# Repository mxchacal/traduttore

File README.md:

# traduttore

https://mxchacal.github.io/traduttore/

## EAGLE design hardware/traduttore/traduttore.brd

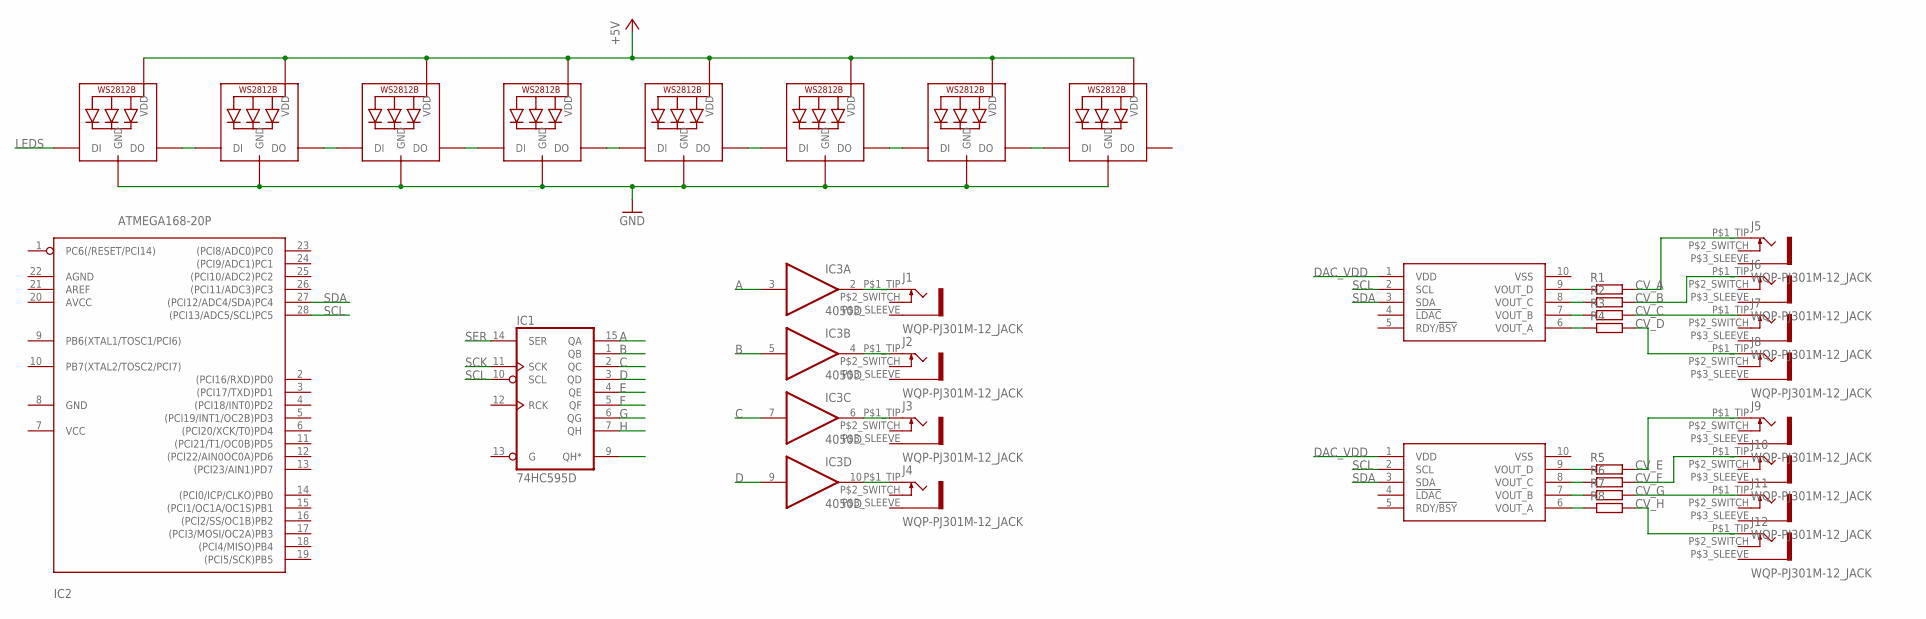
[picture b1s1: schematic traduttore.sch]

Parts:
IC1: 74HC595D; SO16
IC2: ATMEGA168-20P; DIL28-3
IC3: 4050D; SO16
J1, J2, J3, J4, J5, J6, J7, J8, J9, J10, J11, J12: WQP-PJ301M-12_JACK
LED1, LED2, LED3, LED4, LED5, LED6, LED7, LED8: WS2812B5050; WS2812B
R1, R2, R3, R4, R5, R6, R7, R8: R-EU_R0805; R0805
U$1, U$2: MCP4728; MSOP10

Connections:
+5V: LED1.1-VDD (VDD), LED2.1-VDD (VDD), LED3.1-VDD (VDD), LED4.1-VDD (VDD), LED5.1-VDD (VDD), LED6.1-VDD (VDD), LED7.1-VDD (VDD), LED8.1-VDD (VDD)
A: IC1.15 (QA), IC3.3 (I)
B: IC1.1 (QB), IC3.5 (I)
C: IC1.2 (QC), IC3.7 (I)
CV_A: J5.P$1_TIP (2), R1.2
CV_B: J6.P$1_TIP (2), R2.2
CV_C: J7.P$1_TIP (2), R3.2
CV_D: J8.P$1_TIP (2), R4.2
CV_E: J9.P$1_TIP (2), R5.2
CV_F: J10.P$1_TIP (2), R6.2
CV_G: J11.P$1_TIP (2), R7.2
CV_H: J12.P$1_TIP (2), R8.2
D: IC1.3 (QD), IC3.9 (I)
DAC_VDD: U$1.1 (VDD), U$2.1 (VDD)
E: IC1.4 (QE)
F: IC1.5 (QF)
G: IC1.6 (QG)
GND: IC1.8 (GND), LED1.3-GND (GND), LED2.3-GND (GND), LED3.3-GND (GND), LED4.3-GND (GND), LED5.3-GND (GND), LED6.3-GND (GND), LED7.3-GND (GND), LED8.3-GND (GND)
H: IC1.7 (QH)
LEDS: LED1.4-DIN (DI)
unnamed: LED1.2-DOUT (DO), LED2.4-DIN (DI)
unnamed: LED2.2-DOUT (DO), LED3.4-DIN (DI)
unnamed: LED3.2-DOUT (DO), LED4.4-DIN (DI)
unnamed: LED4.2-DOUT (DO), LED5.4-DIN (DI)
unnamed: LED5.2-DOUT (DO), LED6.4-DIN (DI)
unnamed: LED6.2-DOUT (DO), LED7.4-DIN (DI)
unnamed: LED7.2-DOUT (DO), LED8.4-DIN (DI)
unnamed: R1.1, U$1.9 (VOUT_D)
unnamed: R2.1, U$1.8 (VOUT_C)
unnamed: R3.1, U$1.7 (VOUT_B)
unnamed: R4.1, U$1.6 (VOUT_A)
unnamed: IC3.2 (O), J1.P$1_TIP (2)
unnamed: IC3.4 (O), J2.P$1_TIP (2)
unnamed: IC3.6 (O), J3.P$1_TIP (2)
unnamed: IC3.10 (O), J4.P$1_TIP (2)
unnamed: R5.1, U$2.9 (VOUT_D)
unnamed: R6.1, U$2.8 (VOUT_C)
unnamed: R7.1, U$2.7 (VOUT_B)
unnamed: R8.1, U$2.6 (VOUT_A)
SCK: IC1.11 (SCK)
SCL: IC1.10 (SCL), IC2.28 ((PCI13/ADC5/SCL)PC5), U$1.2 (SCL), U$2.2 (SCL)
SDA: IC2.27 ((PCI12/ADC4/SDA)PC4), U$1.3 (SDA), U$2.3 (SDA)
SER: IC1.14 (SER)
VCC: IC1.16 (VCC)
VDD: IC3.1 (VDD)
VSS: IC3.8 (VSS)

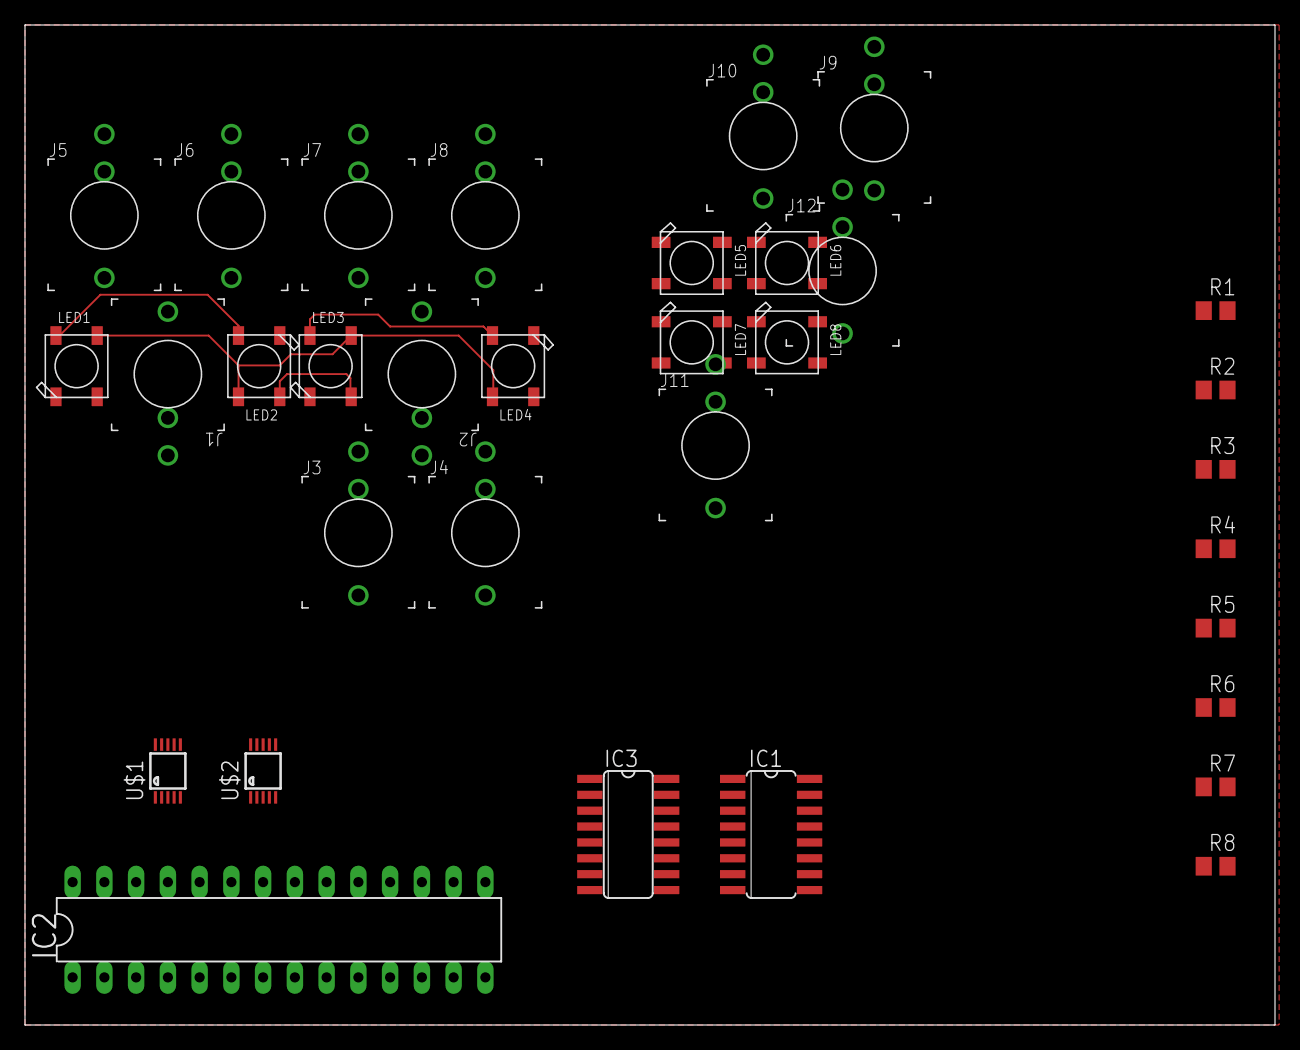
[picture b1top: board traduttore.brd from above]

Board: 2 copper layers, 100.0 x 80.0 mm, 33 parts (0 on the bottom side), 36 nets.

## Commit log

2018-08-13 basic start
2018-08-14 schematics
2018-08-15 test atom io
2018-08-15 test2
